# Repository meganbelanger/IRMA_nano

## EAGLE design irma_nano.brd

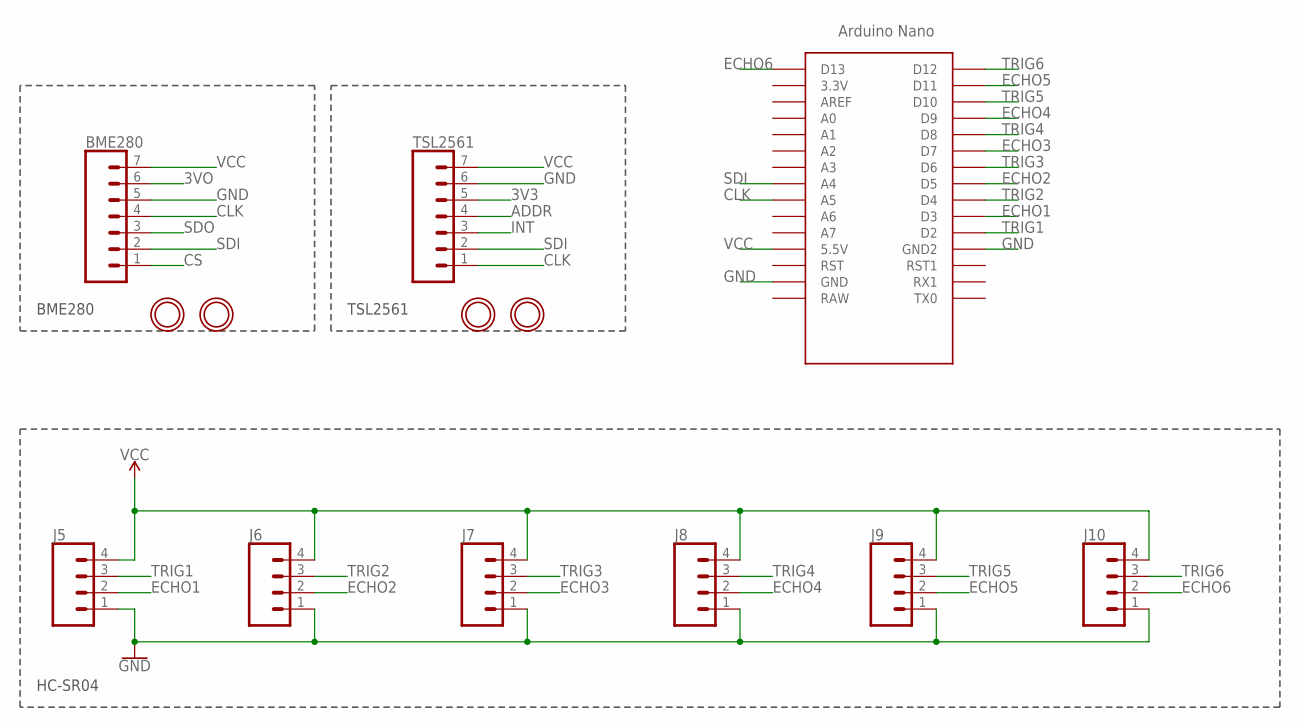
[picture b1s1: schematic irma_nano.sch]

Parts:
BME280: CONN_07; 1X07
J5, J6, J7, J8, J9, J10: CONN_04; 1X04
TSL2561: CONN_07; 1X07
U$1, U$2: MOUNTINGHOLE2.0; MOUNTINGHOLE_2.0_PLATED
U$3, U$4: MOUNTINGHOLE2.5; MOUNTINGHOLE_2.5_PLATED
U$5: NANO

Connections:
3V3: TSL2561.5
3VO: BME280.6
ADDR: TSL2561.4
CLK: BME280.4, TSL2561.1, U$5.A5
CS: BME280.1
ECHO1: J5.2, U$5.D3
ECHO2: J6.2, U$5.D5
ECHO3: J7.2, U$5.D7
ECHO4: J8.2, U$5.D9
ECHO5: J9.2, U$5.D11
ECHO6: J10.2, U$5.D13
GND: BME280.5, J5.1, J6.1, J7.1, J8.1, J9.1, J10.1, TSL2561.6, U$5.GND, U$5.GND1 (GND2)
INT: TSL2561.3
SDI: BME280.2, TSL2561.2, U$5.A4
SDO: BME280.3
TRIG1: J5.3, U$5.D2
TRIG2: J6.3, U$5.D4
TRIG3: J7.3, U$5.D6
TRIG4: J8.3, U$5.D8
TRIG5: J9.3, U$5.D10
TRIG6: J10.3, U$5.D12
VCC: BME280.7, J5.4, J6.4, J7.4, J8.4, J9.4, J10.4, TSL2561.7, U$5.5V (5.5V)

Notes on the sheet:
BME280
TSL2561
HC-SR04

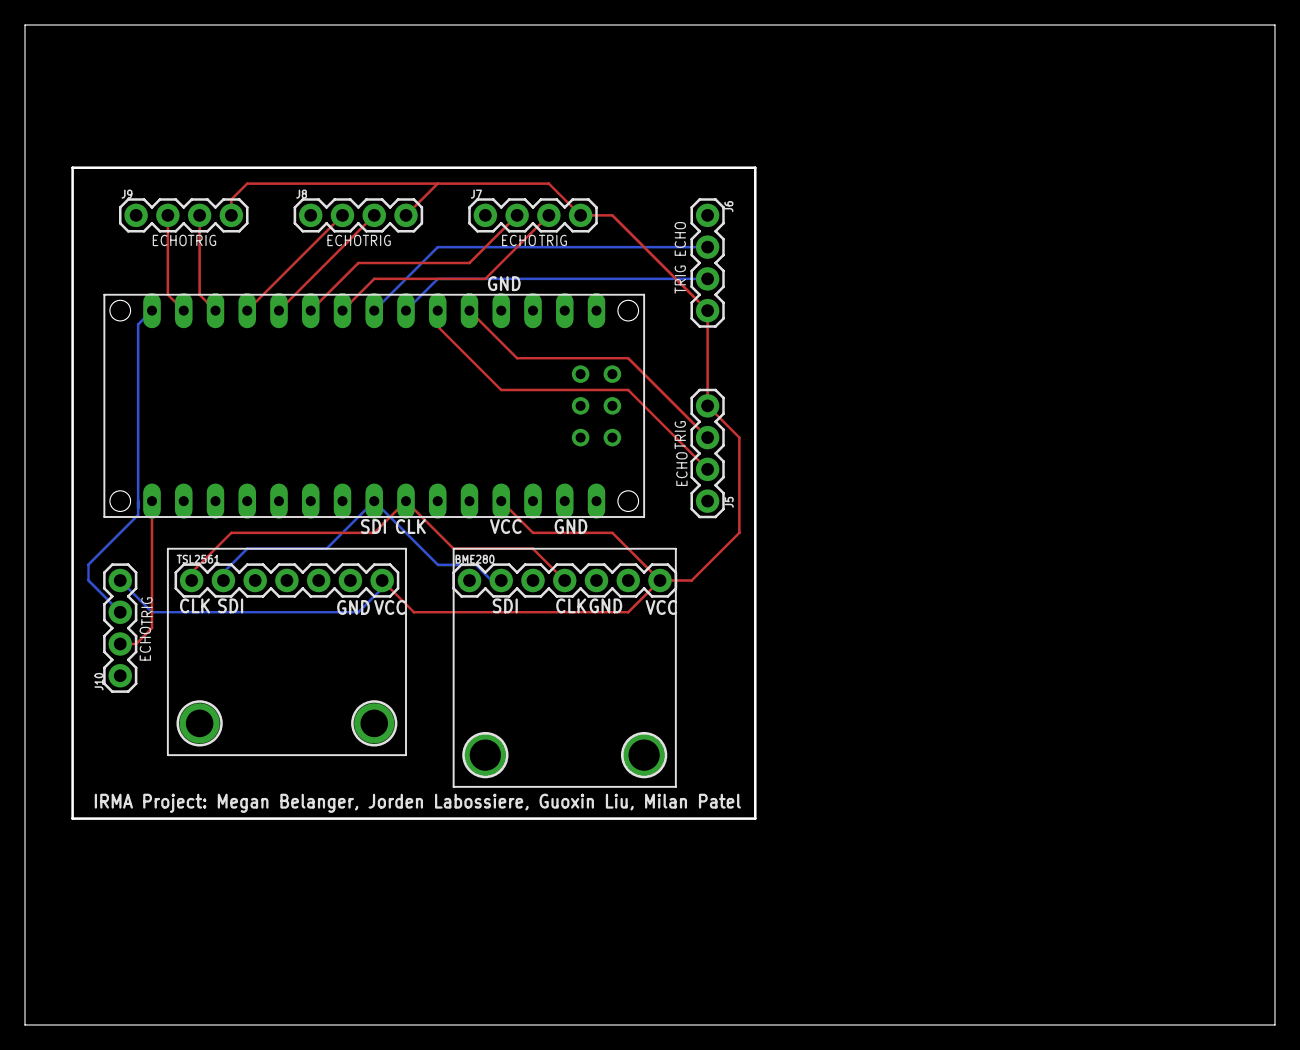
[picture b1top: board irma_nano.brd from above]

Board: 2 copper layers, 100.0 x 80.0 mm, 13 parts (0 on the bottom side), 16 nets.

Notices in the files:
parts and their libraries:
SparkFun-Connectors: Licensing: Creative Commons ShareAlike 4.0 International - https://creativecommons.org/licenses/by-sa/4.0
microbuilder: This work is placed in the public domain, and may be freely used for commercial and non-commercial work with the following conditions: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
